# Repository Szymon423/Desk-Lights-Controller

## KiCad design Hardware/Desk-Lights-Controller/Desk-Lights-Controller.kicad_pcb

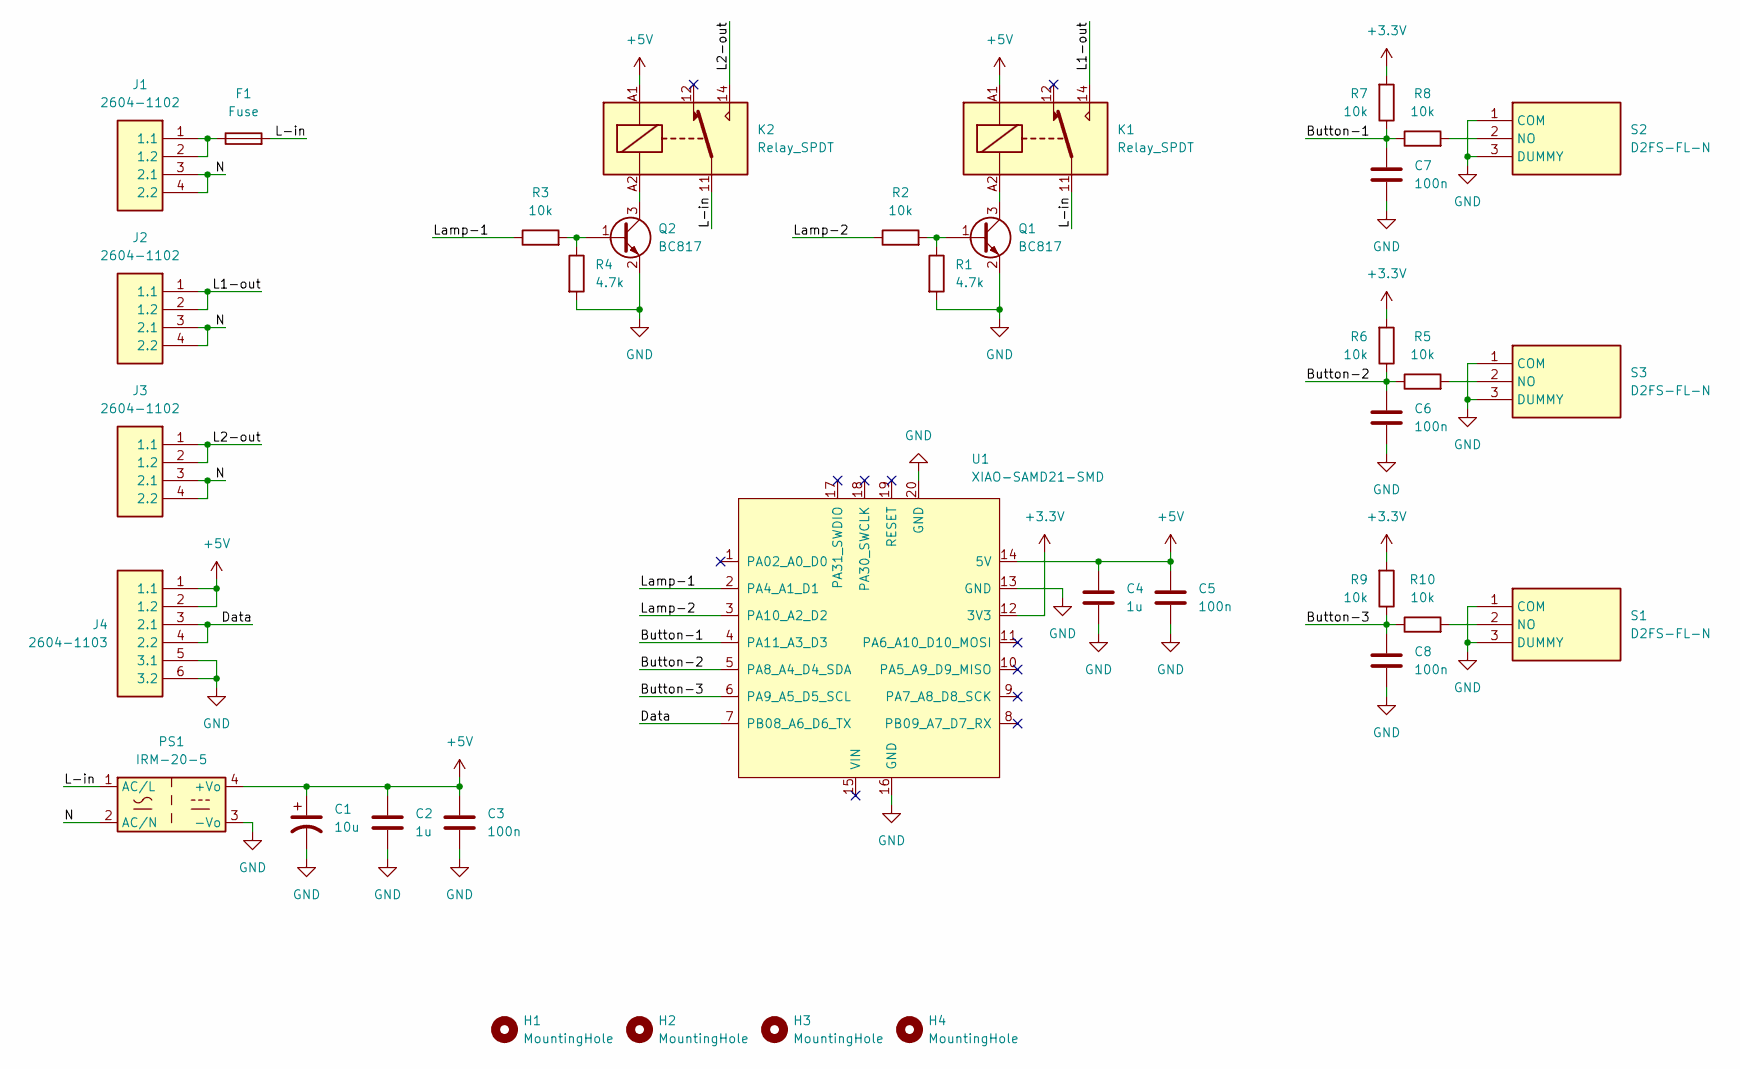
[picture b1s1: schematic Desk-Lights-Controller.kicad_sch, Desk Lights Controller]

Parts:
C1: 10u; CP_Radial_D6.3mm_P2.50mm
C2, C4: 1u; C_0805_2012Metric
C3, C5, C6, C7, C8: 100n; C_0805_2012Metric
F1: Fuse; Fuseholder_Cylinder-5x20mm_Schurter_0031_8201_Horizontal_Op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
H1, H2, H3, H4: MountingHole; MountingHole_3.2mm_M3
J1, J2, J3: 2604-1102; 26041102; Manufacturer_Part_Number 2604-1102
J4: 2604-1103; 26041103; Manufacturer_Part_Number 2604-1102
K1, K2: Relay_SPDT; Relay_SPDT_Finder_40.51
PS1: IRM-20-5; Converter_ACDC_MeanWell_IRM-20-xx_THT
Q1, Q2: BC817; SOT-23
R1, R4: 4.7k; R_0805_2012Metric
R2, R3, R5, R6, R7, R8, R9, R10: 10k; R_0805_2012Metric
S1, S2, S3: D2FS-FL-N; D2FSFLN; Manufacturer_Part_Number D2FS-FL-N
U1: XIAO-SAMD21-SMD

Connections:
+3.3V: R6.2, R7.2, R9.2, U1.12 (3V3)
+5V: C1.1, C2.1, C3.1, C4.1, C5.1, J4.1 (1.1), J4.2 (1.2), K1.A1, K2.A1, PS1.4 (+Vo), U1.14 (5V)
/Button-1: C7.1, R7.1, R8.1, U1.4 (PA11_A3_D3)
/Button-2: C6.1, R5.1, R6.1, U1.5 (PA8_A4_D4_SDA)
/Button-3: C8.1, R9.1, R10.1, U1.6 (PA9_A5_D5_SCL)
/Data: J4.3 (2.1), J4.4 (2.2), U1.7 (PB08_A6_D6_TX)
/L1-out: J2.1 (1.1), J2.2 (1.2), K1.14
/L2-out: J3.1 (1.1), J3.2 (1.2), K2.14
/L-in: F1.2, K1.11, K2.11, PS1.1 (AC/L)
/Lamp-1: R3.1, U1.2 (PA4_A1_D1)
/Lamp-2: R2.1, U1.3 (PA10_A2_D2)
/N: J1.3 (2.1), J1.4 (2.2), J2.3 (2.1), J2.4 (2.2), J3.3 (2.1), J3.4 (2.2), PS1.2 (AC/N)
GND: C1.2, C2.2, C3.2, C4.2, C5.2, C6.2, C7.2, C8.2, J4.5 (3.1), J4.6 (3.2), PS1.3 (-Vo), Q1.2 (E), Q2.2 (E), R1.2, R4.2, S1.1 (COM), S1.3 (DUMMY), S2.1 (COM), S2.3 (DUMMY), S3.1 (COM), S3.3 (DUMMY), U1.13 (GND), U1.16 (GND), U1.20 (GND)
unnamed: F1.1, J1.1 (1.1), J1.2 (1.2)
unnamed: Q1.1 (B), R1.1, R2.2
unnamed: K1.A2, Q1.3 (C)
unnamed: Q2.1 (B), R3.2, R4.1
unnamed: K2.A2, Q2.3 (C)
unnamed: R10.2, S1.2 (NO)
unnamed: R8.2, S2.2 (NO)
unnamed: R5.2, S3.2 (NO)

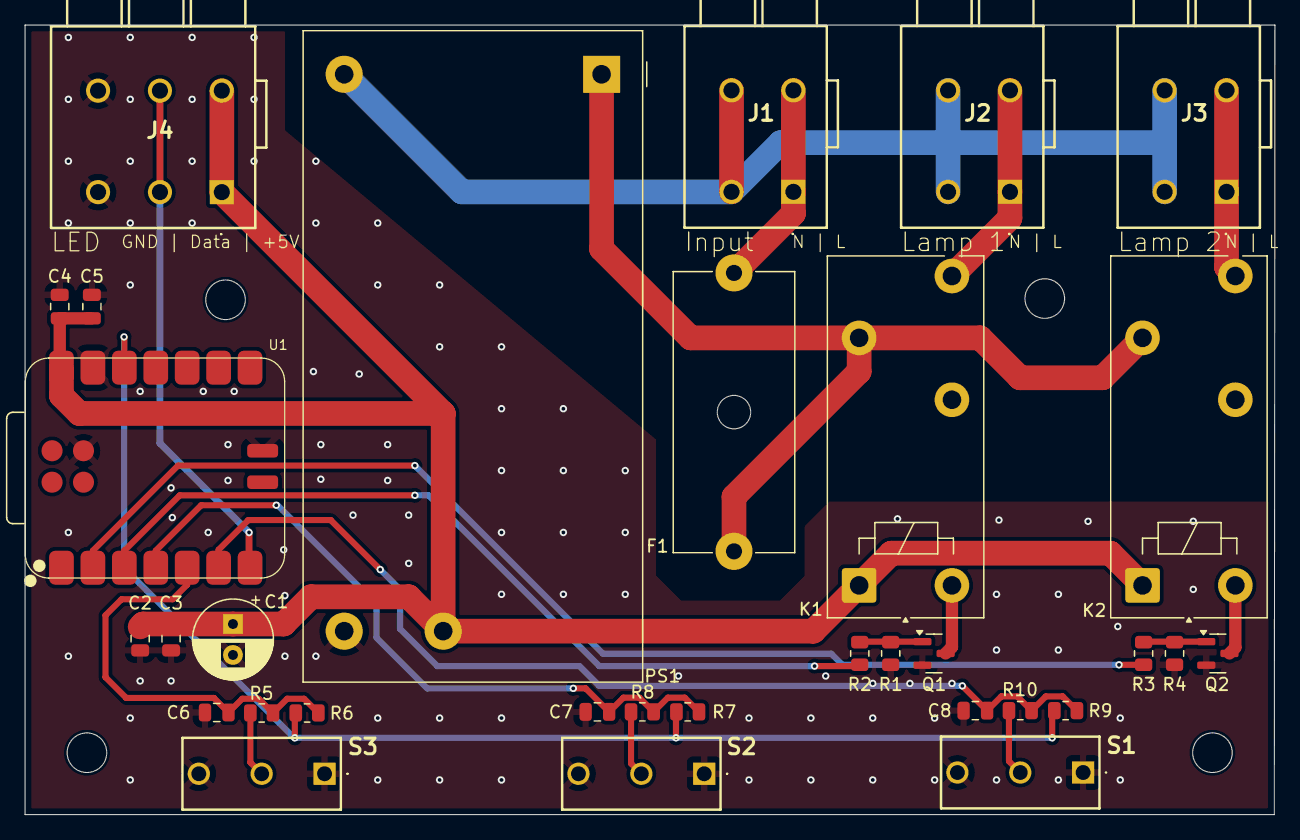
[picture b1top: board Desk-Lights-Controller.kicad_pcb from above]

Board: 2 copper layers, 101.0 x 63.8 mm, 36 parts (0 on the bottom side), 21 nets.

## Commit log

2025-01-02 Added schematics
2025-01-06 Designed PCB, but it might be worth to shrink it a little bit
